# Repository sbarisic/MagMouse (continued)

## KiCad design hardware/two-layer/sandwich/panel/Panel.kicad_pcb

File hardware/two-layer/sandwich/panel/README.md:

# Three-board quotation panel

One 238 × 114 mm, two-layer panel contains one Lower, Upper and Wheel
board. Five panels provide five complete sets. The individual board outlines,
component positions and copper are preserved by translation; nets are isolated
between boards. The panel uses 2 mm routed gaps, 5 mm tabs and 0.6 mm mousebites
on 0.9 mm pitch. The drill row lies outside each finished board outline.

The November circuit correction moves two Wheel tabs to clear the revised
copper: Wheel now has two tabs on its top edge and two on its bottom edge.
The individual board geometry, mounting holes and harness positions are unchanged.

Upload `MagMouse-panel-gerbers.zip` as **Panel by Customer**, **3 designs**,
**5 panels**, FR4, 1.6 mm, 1 oz, green/white, ENIG 1 µin, 0.30 mm minimum via
drill and tented vias. Components, assembly and stencil are separate.

`panelize.py` generates this folder from the three individual boards and checks
exact translated pads, traces, drills and filled copper; connected substrate;
router access; and native KiCad DRC. `panel-manifest.json` records source hashes.
The individual boards also pass ERC, DRC and schematic parity checks, with zero
unconnected nets and zero via-hole/SMD-pad intersections.

This is a quotation package. Supplier CAM approval and prototype electrical,
thermal and enclosure-fit checks remain necessary before production release.

The former Encoder position is panel waste, without its slots or mouse bites.
The three remaining boards retain their positions and outlines.

`Panel-top.png` and `Panel-bottom.png` show copper, fills, pads, vias, silkscreen
and routed edges across the entire panel. The bottom plot is mirrored to show
the physical underside. SVG originals allow inspection at arbitrary zoom.
Regenerate with `../render_panel.py`.

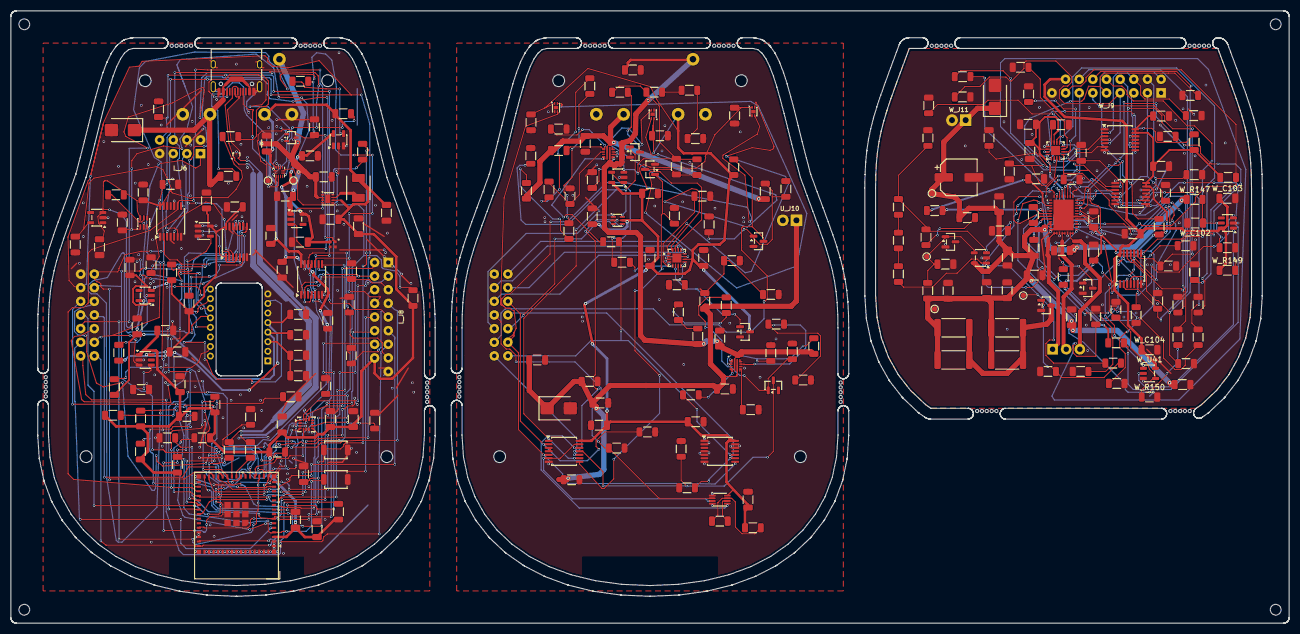
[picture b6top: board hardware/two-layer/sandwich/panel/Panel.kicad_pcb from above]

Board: 2 copper layers, 238.0 x 114.0 mm, 345 parts (0 on the bottom side), 182 nets.

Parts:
L_C1, L_C2, L_C3, L_C5, L_C23, L_C73, L_C74, L_C77, L_C78: 10uF/25V; C_1206_3216Metric
L_C4, L_C55, L_C63, L_C64: 1uF/50V; C_1206_3216Metric
L_C6, L_C22, L_C53, L_C70, L_C75, L_C76, L_C80, L_C83, L_C85, L_C86, L_C87: 100nF; C_1206_3216Metric
L_C71, L_C81, L_C82: 2.2uF/10V; C_1206_3216Metric
L_C72: 10nF; C_1206_3216Metric_OneSideSilk
L_C79: 1nF/50V; C_1206_3216Metric
L_C84: 4.7uF/10V; C_1206_3216Metric
L_C105: 100nF/50V; C_1206_3216Metric
L_D1: SMBJ12A; D_SMB
L_D5: SK6805-EC15; OPSCO_SK6805_EC15
L_H101, L_H102, L_H103, L_H104: M2 clearance / 5mm support envelope; MountingHole_2.2mm_M2_5mm_Envelope
L_J1: TYPE-C-31-M-12; USB_C_Receptacle_HRO_TYPE-C-31-M-12
L_J6: GB1806 AS5048A encoder wires; Wire_Signal_2x04_P2.54mm
L_J8: Wheel 17-wire signals / 2 GND; Wire_Wheel_17_P2.54mm
L_J101: Stack signals / 14 wires; Wire_Stack_Signal_14
L_J103: Stack power / 5 wires; Wire_Stack_Power_5
L_L1: SRP4020CC-3R3M; L_Bourns_SRP4020CC
L_R3, L_R4, L_R7, L_R72, L_R73, L_R74, L_R75, L_R76, L_R77, L_R78, L_R79, L_R80, L_R99, L_R126, L_R127, L_R130, L_R131, L_R135: 10k; R_1206_3216Metric
L_R5, L_R6: 33R; R_1206_3216Metric
L_R25: 887k; R_1206_3216Metric
L_R26, L_R27, L_R101, L_R110, L_R129, L_R133, L_R134, L_R136: 100k; R_1206_3216Metric
L_R28: 1k; R_1206_3216Metric
L_R125: 0R; R_1206_3216Metric
L_R128: 330R; R_1206_3216Metric
L_R132: 39R; R_1206_3216Metric
L_R141, L_R142, L_R143: 33k; R_1206_3216Metric
L_SW1: RESET; SW_SPST_TS-1088-xR020
L_SW2: BOOT; SW_SPST_TS-1088-xR020
L_TP38: RGB_5V; TestPoint_Pad_D1.0mm
L_TP39: RGB_DIN; TestPoint_Pad_D1.0mm
L_U1: TPD2EUSB30DRTR; Texas_DRT-3
L_U2: TPS62162DSGR; Texas_DSG0008A_WSON-8-1EP_2x2mm_P0.5mm_EP0.9x1.6mm
L_U3: ESP32-S3-MINI-1-N8; ESP32-S2-MINI-1
L_U11: TUSB320LAIRWBR; Texas_X2QFN-12_1.6x1.6mm_P0.4mm
L_U20: TPD2E2U06DCKR; SOT-323_SC-70
L_U25, L_U29, L_U37: 74LVC125APW,118; TSSOP-14_4.4x5mm_P0.65mm
L_U28: TPS22919DCKR; SOT-363_SC-70-6
L_U32: ICM-42688-P; LGA-14_3x2.5mm_P0.5mm_LayoutBorder3x4y
L_U33: TPS7A2450DBVR; SOT-23-5
L_U34: SN74LV1T34DBVR; SOT-23-5
L_U35: PMW3360DM-T2QU; PixArt_PMW3360DM_T2QU
L_U36: TLV75519PDBVR; SOT-23-5
L_U38: TPS22918DBVR; SOT-23-6
L_U39: SN74LVC1G125DBVR; SOT-23-5
L_U42: TLV75533PDBVR; SOT-23-5
MB1_1, MB1_2, MB1_3, MB1_4, MB1_5, MB2_1, MB2_2, MB2_3, MB2_4, MB2_5, MB3_1, MB3_2, MB3_3, MB3_4, MB3_5, MB4_1, MB4_2, MB4_3, MB4_4, MB4_5, MB5_1, MB5_2, MB5_3, MB5_4, MB5_5, MB6_1, MB6_2, MB6_3, MB6_4, MB6_5, MB7_1, MB7_2, MB7_3, MB7_4, MB7_5, MB8_1, MB8_2, MB8_3, MB8_4, MB8_5, MB9_1, MB9_2, MB9_3, MB9_4, MB9_5, MB10_1, MB10_2, MB10_3, MB10_4, MB10_5, MB11_1, MB11_2, MB11_3, MB11_4, MB11_5, MB12_1, MB12_2, MB12_3, MB12_4, MB12_5: NPTH
TOOL1, TOOL2, TOOL3, TOOL4: NPTH
U_C16, U_C17, U_C18, U_C28, U_C29, U_C31, U_C32, U_C33, U_C34, U_C35, U_C36: 100nF; C_1206_3216Metric
U_C19, U_C20, U_C21, U_C24, U_C27, U_C89: 1uF/50V; C_1206_3216Metric
U_C25, U_C26: 10nF; C_1206_3216Metric
U_C37, U_C38, U_C39, U_C40, U_C88: 10uF/25V; C_1206_3216Metric
U_D2: SMBJ6.0A; D_SMB
U_D3, U_D4: BAT54-7-F; SOT-23
U_H105, U_H106, U_H107, U_H108: M2 clearance / 5mm support envelope; MountingHole_2.2mm_M2_5mm_Envelope
U_J10: Soldered wires Power_1x02; Wire_Power_1x02_P2.54mm
U_J102: Stack signals / 14 wires; Wire_Stack_Signal_14
U_J104: Stack power / 5 wires; Wire_Stack_Power_5
U_Q1, U_Q2, U_Q3: 2N7002; SOT-23
U_R29, U_R41, U_R65, U_R68: 22.1k; R_1206_3216Metric
U_R30, U_R36, U_R37, U_R38, U_R46, U_R47, U_R48, U_R49, U_R61, U_R70: 10k; R_1206_3216Metric
U_R31, U_R32, U_R33, U_R34, U_R35, U_R40, U_R62, U_R63, U_R66, U_R67, U_R71: 100k; R_1206_3216Metric
U_R39: 11k; R_1206_3216Metric
U_R42, U_R43, U_R56, U_R57, U_R60: 3.3k; R_1206_3216Metric
U_R44, U_R45, U_R64, U_R69: 1k; R_1206_3216Metric
U_R58: 33R; R_1206_3216Metric
U_R59: 4.7k; R_1206_3216Metric
U_U7, U_U8, U_U9: TMAG5253BA2IQDMRR; Texas_X2SON-4-1EP_1.1x1.4mm_P0.5mm_EP0.8x0.6mm
U_U10: ADS7038IRTER; WQFN-16-1EP_3x3mm_P0.5mm_EP1.68x1.68mm
U_U12, U_U13: TPS259470LRPWR; Texas_RPW0010A
U_U14: SN74LVC2G04DCKR; SOT-363_SC-70-6
U_U15: SN74LVC1G123DCUR; VSSOP-8_2.3x2mm_P0.5mm
U_U16, U_U18: SN74LVC08APWR; TSSOP-14_4.4x5mm_P0.65mm
U_U19: TLV9001IDBVR; SOT-23-5
W_C41, W_C42, W_C43, W_C49, W_C51, W_C52, W_C54, W_C65, W_C66: 100nF; C_1206_3216Metric
W_C44, W_C45, W_C68, W_C69: 10uF/25V; C_1206_3216Metric
W_C46, W_C48, W_C56, W_C57, W_C58: 1uF/50V; C_1206_3216Metric
W_C47: 47nF/50V; C_1206_3216Metric
W_C50: 22uF/25V; C_1206_3216Metric
W_C59, W_C60, W_C61, W_C67: 22pF/50V; C_1206_3216Metric
W_C90: 100uF/16V; CP_Elec_6.3x5.9
W_C102: 1nF/50V; C_1206_3216Metric
W_C103, W_C104: 100nF/50V; C_1206_3216Metric
W_D6: SMBJ6.0A; D_SMB
W_J5: GB1806 phase wires; MotorWire_3x1mm_P2.54mm
W_J9: Wheel 17-wire signals / 2 GND; Wire_Wheel_17_P2.54mm
W_J11: Soldered wires Power_1x02; Wire_Power_1x02_P2.54mm
W_Q4: 2N7002; SOT-23
W_Q5: AO3400A; SOT-23
W_R81: 22R; R_1206_3216Metric
W_R82, W_R84, W_R86, W_R98, W_R111, W_R137, W_R138, W_R139, W_R140, W_R148, W_R149: 10k; R_1206_3216Metric
W_R83, W_R89, W_R90, W_R91, W_R92, W_R94, W_R95, W_R96, W_R97, W_R100, W_R112, W_R114, W_R120, W_R150: 100k; R_1206_3216Metric
W_R87, W_R88, W_R146: 4.7k; R_1206_3216Metric
W_R102, W_R103, W_R104: 330R; R_1206_3216Metric
W_R105, W_R106, W_R107, W_R108, W_R109: 0R; R_1206_3216Metric
W_R113: 34.8k; R_1206_3216Metric
W_R115, W_R116, W_R117: 1M; R_1206_3216Metric
W_R119: 100R; R_1206_3216Metric
W_R121, W_R122, W_R123, W_R124: 47R/2W; R_2512_6332Metric
W_R144, W_R145: 33k; R_1206_3216Metric
W_R147: 105k; R_1206_3216Metric
W_TP34: ACT_5V; TestPoint_Pad_D1.0mm
W_TP35: BRAKE_REF; TestPoint_Pad_D1.0mm
W_TP36: BRAKE_OUT; TestPoint_Pad_D1.0mm
W_TP37: GND; TestPoint_Pad_D1.0mm
W_U21: DRV8316RRGFR; Texas_RGF0040E
W_U22: SN74LVC08APWR; TSSOP-14_4.4x5mm_P0.65mm
W_U23: ADS7038IRTER; WQFN-16-1EP_3x3mm_P0.5mm_EP1.68x1.68mm
W_U24: 74LVC125APW,118; TSSOP-14_4.4x5mm_P0.65mm_InsetPin1
W_U26: 74LVC125APW,118; TSSOP-14_4.4x5mm_P0.65mm
W_U30: TLV1811DBVR; SOT-23-5
W_U31: LM4040AIM3-2.5/NOPB; SOT-23
W_U40: TPS3808G01DBVR; SOT-23-6
W_U41: SN74LVC1G08DBVR; SOT-23-5

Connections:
Lower/+3V3: L_C2.1, L_C3.1, L_C5.1, L_C6.1, L_C22.1, L_C23.1, L_C53.1, L_C70.1, L_C71.1, L_C72.1, L_C77.1, L_C78.1, L_J8.16, L_J103.4, L_L1.2, L_R3.1, L_R4.1, L_R7.1, L_R26.1, L_R27.1, L_R72.1, L_R73.1, L_R74.1, L_R75.1, L_R76.1, L_R127.1, L_U2.6, L_U3.3, L_U11.12, L_U25.14, L_U32.5, L_U32.8, L_U38.1
Lower/ACT_DRIVE_EN: L_J8.13, L_J101.13
Lower/ACT_HEARTBEAT: L_J101.7, L_U3.21
Lower/ACT_REQ: L_J101.6, L_U3.20
Lower/ADC2_MISO_LOCAL: L_J8.9, L_R143.1, L_U25.9
Lower/ADC_CS: L_J101.5, L_R7.2, L_U3.14
Lower/BOOT: L_R4.2, L_SW2.1, L_U3.4
Lower/BOOT_SAFE_SPARE: L_R80.1, L_U3.44
Lower/BUCK_SW: L_L1.1, L_U2.7
Lower/CC_OUT1: L_J101.9, L_R26.2, L_U3.18, L_U11.7
Lower/CC_OUT2: L_J101.10, L_R27.2, L_U3.19, L_U11.8
Lower/CC_VBUS_DET: L_R25.2, L_U11.4
Lower/CS_ADC2: L_J8.8, L_R74.2, L_U3.32, L_U25.10
Lower/CS_DRV8316: L_J8.4, L_R76.2, L_U3.34, L_U25.1
Lower/CS_ENCODER: L_R75.2, L_U3.33, L_U25.4, L_U29.9
Lower/CS_IMU: L_R73.2, L_U3.25, L_U32.12
Lower/CS_PAW: L_R72.2, L_U3.6, L_U37.1, L_U37.4, L_U37.10, L_U39.2
Lower/DRV_FAULT_LOCAL_N: L_J8.15, L_R141.1, L_U25.12
Lower/DRV_FAULT_N: L_U3.37, L_U25.11
Lower/DRV_MISO_LOCAL: L_J8.5, L_R142.1, L_U25.2
Lower/ENC_3V3: L_C64.1, L_C105.1, L_R99.1, L_U29.13, L_U29.14, L_U42.5
Lower/ENC_5V: L_C55.1, L_J6.1, L_R125.2, L_U28.6, L_U42.1, L_U42.3
Lower/ENC_CS_LOCAL: L_J6.6, L_R99.2, L_U29.8
Lower/ENC_MISO_LOCAL: L_J6.8, L_R101.1, L_U25.5
Lower/ENC_MOSI_LOCAL: L_J6.5, L_U29.6
Lower/ENC_QOD: L_R125.1, L_U28.5
Lower/ENC_SCLK_LOCAL: L_J6.3, L_U29.3
Lower/GND: L_C1.2, L_C2.2, L_C3.2, L_C4.2, L_C5.2, L_C6.2, L_C22.2, L_C23.2, L_C53.2, L_C55.2, L_C63.2, L_C64.2, L_C70.2, L_C71.2, L_C72.2, L_C73.2, L_C74.2, L_C75.2, L_C76.2, L_C77.2, L_C78.2, L_C79.2, L_C80.2, L_C81.2, L_C82.2, L_C83.2, L_C84.2, L_C85.2, L_C86.2, L_C87.2, L_C105.2, L_D1.2, L_D5.4, L_J1.A1, L_J1.A12, L_J1.B1, L_J1.B12, L_J1.SH, L_J6.2, L_J6.4, L_J6.7, L_J8.1, L_J8.17, L_J101.1, L_J103.1, L_J103.5, L_R77.2, L_R78.2, L_R79.2, L_R80.2, L_R101.2, L_R110.2, L_R126.2, L_R129.2, L_R130.2, L_R134.2, L_R141.2, L_R142.2, L_R143.2, L_SW1.2, L_SW2.2, L_U1.3, L_U2.1, L_U2.4, L_U2.5, L_U2.9, L_U3.1, L_U3.2, L_U3.42, L_U3.43, L_U3.46, L_U3.47, L_U3.48, L_U3.49, L_U3.50, L_U3.51, L_U3.52, L_U3.53, L_U3.54, L_U3.55, L_U3.56, L_U3.57, L_U3.58, L_U3.59, L_U3.60, L_U3.61, L_U3.62, L_U3.63, L_U3.64, L_U3.65, L_U11.3, L_U11.10, L_U11.11, L_U20.3, L_U25.7, L_U25.13, L_U28.2, L_U29.1, L_U29.4, L_U29.7, L_U29.10, L_U29.12, L_U32.6, L_U32.7, L_U33.2, L_U34.3, L_U35.8, L_U36.2, L_U37.7, L_U37.13, L_U38.2, L_U39.1, L_U39.3, L_U42.2
Lower/HALL_EN: L_J101.12, L_R110.1, L_U28.3, L_U33.3, L_U38.3
Lower/IMU_INT1: L_R127.2, L_U3.36, L_U32.4
Lower/IMU_PIN9: L_R126.1, L_U32.9
Lower/LOGIC_PG: L_R28.1, L_U2.8
Lower/MCU_EN: L_C4.1, L_J101.14, L_R3.2, L_R28.2, L_SW1.1, L_U3.45
Lower/MCU_USB_DM: L_R5.1, L_U3.23
Lower/MCU_USB_DP: L_R6.1, L_U3.24
Lower/MOTOR_SPI_MISO: L_U3.31, L_U25.8
Lower/MOTOR_SPI_MOSI: L_J8.7, L_U3.28
Lower/MOTOR_SPI_SCLK: L_J8.6, L_U3.29
Lower/OPT_1V9: L_C82.1, L_C83.1, L_R132.1, L_U35.4, L_U36.5
Lower/OPT_3V3: L_C80.1, L_C81.1, L_C86.1, L_C87.1, L_R131.1, L_R133.1, L_R135.1, L_R136.1, L_U35.5, L_U36.1, L_U36.3, L_U37.14, L_U38.6, L_U39.5
Lower/OPT_CS_N: L_R131.2, L_U35.13, L_U39.4
Lower/OPT_CTRL: L_R79.1, L_U3.26, L_U37.12
Lower/OPT_LED_P: L_R132.2, L_U35.15
Lower/OPT_MISO: L_R135.2, L_U35.12, L_U37.9
Lower/OPT_MOSI: L_R134.1, L_U35.11, L_U37.3
Lower/OPT_RAMP_CT: L_C79.1, L_U38.4
Lower/OPT_RESET_N: L_U35.7, L_U37.11
Lower/OPT_SCLK: L_R133.2, L_U35.10, L_U37.6
Lower/OPT_VDDPIX: L_C84.1, L_C85.1, L_U35.3
Lower/PAW_MOTION_N: L_R136.2, L_U3.35, L_U35.9
Lower/PWR_5V: L_C1.1, L_C73.1, L_J103.3, L_U2.2, L_U2.3, L_U33.1
Lower/RGB_5V: L_C63.1, L_C74.1, L_C75.1, L_C76.1, L_D5.2, L_R130.1, L_TP38.1, L_U28.1, L_U33.5, L_U34.5
Lower/RGB_BUFFER_OUT: L_R128.1, L_U34.4
Lower/RGB_DATA: L_R78.1, L_U3.41, L_U34.2
Lower/RGB_DIN: L_D5.1, L_R128.2, L_R129.1, L_TP39.1
Lower/SENS_REQ: L_J101.8, L_U3.22
Lower/SPI_MISO: L_J101.4, L_U3.17, L_U25.3, L_U25.6, L_U32.1, L_U37.8
Lower/SPI_MOSI: L_J8.3, L_J101.3, L_U3.15, L_U29.5, L_U32.14, L_U37.2
Lower/SPI_SCLK: L_J8.2, L_J101.2, L_U3.16, L_U29.2, L_U32.13, L_U37.5
Lower/USB_CC1: L_J1.A5, L_U11.1, L_U20.1
Lower/USB_CC2: L_J1.B5, L_U11.2, L_U20.2
Lower/USB_DM: L_J1.A7, L_J1.B7, L_R5.2, L_U1.2
Lower/USB_DP: L_J1.A6, L_J1.B6, L_R6.2, L_U1.1
Lower/VBUS_PRESENT_N: L_J101.11, L_U3.5
Lower/VBUS_USB: L_D1.1, L_J1.A4, L_J1.A9, L_J1.B4, L_J1.B9, L_J103.2, L_R25.1
Lower/WHEEL_PWM_A: L_J8.10, L_U3.38
Lower/WHEEL_PWM_B: L_J8.11, L_U3.27
Lower/WHEEL_PWM_C: L_J8.12, L_U3.30
Lower/WHEEL_RUN_REQ: L_J8.14, L_R77.1, L_U3.7
Upper/+3V3: U_C16.1, U_C17.1, U_C18.1, U_C19.1, U_C20.1, U_C28.1, U_C29.1, U_C31.1, U_C32.1, U_C34.1, U_D4.3, U_J104.4, U_R46.1, U_R71.1, U_U7.1, U_U8.1, U_U9.1, U_U10.7, U_U10.10, U_U14.5, U_U15.8, U_U16.14, U_U18.14, U_U19.5
Upper/ACT_5V: U_C37.1, U_C38.1, U_C39.1, U_C40.1, U_D2.1, U_J10.1, U_R67.1, U_R69.1, U_U13.6
Upper/ACT_DRIVE_EN: U_D3.3, U_J102.13, U_R49.1, U_U16.11
Upper/ACT_DVDT: U_C26.1, U_U13.7
Upper/ACT_FAULT_N: U_R45.1, U_U13.4
Upper/ACT_HEARTBEAT: U_J102.7, U_R47.1, U_U15.2
Upper/ACT_ILM: U_R42.1, U_R43.1, U_U13.9
Upper/ACT_OVLO: U_R40.2, U_R41.1, U_U13.2
Upper/ACT_PERMIT: U_U15.5, U_U16.12
Upper/ACT_REQ: U_J102.6, U_R48.1, U_U16.2
Upper/ACT_UVLO: U_D3.1, U_R38.2, U_R39.1, U_U13.1
Upper/ACT_UV_1: U_R36.2, U_R37.1
Upper/ACT_UV_2: U_R37.2, U_R38.1
Upper/ACT_VMON: U_C36.1, U_D4.1, U_R67.2, U_R68.1, U_U10.6
Upper/ADC_CS: U_J102.5, U_U10.11
Upper/ADC_DECAP: U_C21.1, U_U10.8
Upper/ARM_SOURCE: U_U16.3, U_U16.4
Upper/ARM_VALID: U_U15.3, U_U16.6, U_U16.13
Upper/CC_OUT1: U_J102.9, U_U14.1
Upper/CC_OUT2: U_J102.10, U_U14.3
Upper/CC_OUT2_INV: U_U14.4, U_U16.10
Upper/GND: U_C16.2, U_C17.2, U_C18.2, U_C19.2, U_C20.2, U_C21.2, U_C24.2, U_C25.2, U_C26.2, U_C28.2, U_C29.2, U_C31.2, U_C32.2, U_C33.2, U_C34.2, U_C35.2, U_C36.2, U_C37.2, U_C38.2, U_C39.2, U_C40.2, U_C88.2, U_C89.2, U_D2.2, U_J10.2, U_J102.1, U_J104.1, U_J104.5, U_Q1.2, U_Q2.2, U_Q3.2, U_R30.2, U_R35.2, U_R39.2, U_R41.2, U_R42.2, U_R43.2, U_R47.2, U_R48.2, U_R49.2, U_R58.2, U_R62.2, U_R63.2, U_R66.2, U_R68.2, U_R69.2, U_R70.2, U_U7.2, U_U7.5, U_U8.2, U_U8.5, U_U9.2, U_U9.5, U_U10.2, U_U10.3, U_U10.4, U_U10.9, U_U10.17, U_U12.8, U_U13.8, U_U14.2, U_U15.1, U_U15.4, U_U16.7, U_U18.1, U_U18.2, U_U18.4, U_U18.5, U_U18.7, U_U18.12, U_U18.13, U_U19.2
Upper/HALL_EN: U_J102.12, U_U7.3, U_U8.3, U_U9.3, U_U16.5, U_U18.8
Upper/HALL_L: U_U7.4, U_U10.15
Upper/HALL_M: U_U8.4, U_U10.16
Upper/HALL_R: U_U9.4, U_U10.1
Upper/ILM_BASE_1: U_R56.2, U_R57.1
Upper/ILM_BASE_2: U_R57.2, U_R58.1
Upper/ILM_HIGH_D: U_Q2.3, U_R60.2, U_R61.2
Upper/ILM_MED_D: U_Q1.3, U_R59.2
Upper/MCU_EN: U_J102.14, U_R44.2, U_R45.2, U_U18.10
Upper/PWR_5V: U_C88.1, U_C89.1, U_J104.3, U_R36.1, U_R40.1, U_U12.6, U_U13.5
Upper/SENS_REQ: U_J102.8, U_R70.1, U_U18.9
Upper/SOURCE_3A: U_Q2.1, U_R63.1, U_U16.8
Upper/SOURCE_OK: U_Q1.1, U_R62.1, U_U14.6, U_U16.1, U_U16.9
Upper/SPI_MISO: U_J102.4, U_U10.12
Upper/SPI_MOSI: U_J102.3, U_U10.14
Upper/SPI_SCLK: U_J102.2, U_U10.13
Upper/USB_DVDT: U_C25.1, U_U12.7
Upper/USB_FAULT_N: U_R44.1, U_U12.4
Upper/USB_ILM: U_R56.1, U_R59.1, U_R60.1, U_R61.1, U_U12.9, U_U19.3
Upper/USB_IMON_ADC: U_C33.1, U_R64.2, U_U10.5
Upper/USB_IMON_BUF: U_R64.1, U_U19.1, U_U19.4
Upper/USB_OVLO: U_R34.2, U_R35.1, U_U12.2
Upper/USB_OV_1: U_R31.2, U_R32.1
Upper/USB_OV_2: U_R32.2, U_R33.1
Upper/USB_OV_3: U_R33.2, U_R34.1
Upper/USB_UVLO: U_R29.2, U_R30.1, U_U12.1
Upper/VBUS_GATE: U_C35.1, U_Q3.1, U_R65.2, U_R66.1
Upper/VBUS_PRESENT_N: U_J102.11, U_Q3.3, U_R71.2
Upper/VBUS_USB: U_C24.1, U_J104.2, U_R29.1, U_R31.1, U_R65.1, U_U12.5
Upper/WD_CEXT: U_C27.2, U_U15.6
Upper/WD_RCEXT: U_C27.1, U_R46.2, U_U15.7
Wheel/+3V3: W_C51.1, W_C103.1, W_C104.1, W_J9.16, W_R149.1, W_U22.14, W_U40.6, W_U41.5
Wheel/ACT_5V: W_C41.1, W_C42.1, W_C43.1, W_C44.1, W_C45.1, W_C46.2, W_C65.1, W_C68.1, W_C69.1, W_C90.1, W_D6.1, W_J11.1, W_R111.1, W_R112.1, W_R121.1, W_R122.1, W_R123.1, W_R124.1, W_R146.1, W_R147.1, W_TP34.1, W_U21.9, W_U21.10, W_U21.11, W_U30.5
Wheel/ACT_DRIVE_EN: W_J9.13, W_R84.1, W_U21.23, W_U22.1, W_U40.3
Wheel/ADC2_CS_LOCAL: W_R98.2, W_U23.11, W_U26.8
Wheel/ADC2_DECAP: W_C58.1, W_U23.8
Wheel/ADC2_MISO_LOCAL: W_J9.9, W_R100.1, W_U23.12
Wheel/ADC2_MOSI_LOCAL: W_U23.14, W_U26.6
Wheel/ADC2_SCLK_LOCAL: W_U23.13, W_U26.3
Wheel/ADC2_SPARE3: W_R105.1, W_U23.2
Wheel/ADC2_SPARE4: W_R106.1, W_U23.3
Wheel/ADC2_SPARE5: W_R107.1, W_U23.4
Wheel/ADC2_SPARE6: W_R108.1, W_U23.5
Wheel/ADC2_SPARE7: W_R109.1, W_U23.6
Wheel/BRAKE_DIV_TOP: W_R112.2, W_R113.1
Wheel/BRAKE_DRAIN: W_Q5.3, W_R121.2, W_R122.2, W_R123.2, W_R124.2
Wheel/BRAKE_FB_1: W_R115.2, W_R116.1
Wheel/BRAKE_FB_2: W_R116.2, W_R117.1
Wheel/BRAKE_GATE: W_Q5.1, W_R119.2, W_R120.1
Wheel/BRAKE_OUT: W_R115.1, W_R119.1, W_TP36.1, W_U30.1
Wheel/BRAKE_REF: W_C66.1, W_R111.2, W_TP35.1, W_U30.4, W_U31.1
Wheel/BRAKE_SENSE: W_C67.1, W_R113.2, W_R114.1, W_R117.2, W_U30.3
Wheel/CS_ADC2: W_J9.8, W_R145.1, W_U26.9
Wheel/CS_DRV8316: W_J9.4, W_R144.1, W_U24.9
Wheel/DRV_AVDD: W_C48.1, W_C49.1, W_C52.1, W_C54.1, W_C56.1, W_C57.1, W_R82.1, W_R86.1, W_R87.1, W_R88.1, W_R98.1, W_U21.25, W_U21.37, W_U23.7, W_U23.10, W_U24.13, W_U24.14, W_U26.13, W_U26.14
Wheel/DRV_CS_LOCAL: W_R86.2, W_U21.36, W_U24.8
Wheel/DRV_FAULT_LOCAL_N: W_J9.15, W_R88.2, W_R89.1, W_U21.22
Wheel/DRV_INHA: W_R90.1, W_U21.27, W_U22.6
Wheel/DRV_INHB: W_R91.1, W_U21.29, W_U22.8
Wheel/DRV_INHC: W_R92.1, W_U21.31, W_U22.11
Wheel/DRV_MISO_LOCAL: W_J9.5, W_R87.2, W_U21.33
Wheel/DRV_MOSI_LOCAL: W_U21.34, W_U24.6
Wheel/DRV_SCLK_LOCAL: W_U21.35, W_U24.3
Wheel/GND: W_C41.2, W_C42.2, W_C43.2, W_C44.2, W_C45.2, W_C48.2, W_C49.2, W_C50.2, W_C51.2, W_C52.2, W_C54.2, W_C56.2, W_C57.2, W_C58.2, W_C59.2, W_C60.2, W_C61.2, W_C65.2, W_C66.2, W_C67.2, W_C68.2, W_C69.2, W_C90.2, W_C102.2, W_C103.2, W_C104.2, W_D6.2, W_J9.1, W_J9.17, W_J11.2, W_Q4.2, W_Q5.2, W_R83.2, W_R84.2, W_R89.2, W_R90.2, W_R91.2, W_R92.2, W_R94.2, W_R95.2, W_R96.2, W_R97.2, W_R100.2, W_R105.2, W_R106.2, W_R107.2, W_R108.2, W_R109.2, W_R114.2, W_R120.2, W_R137.2, W_R138.2, W_R139.2, W_R140.2, W_R144.2, W_R145.2, W_R146.2, W_R148.2, W_R150.2, W_TP37.1, W_U21.2, W_U21.4, W_U21.12, W_U21.15, W_U21.18, W_U21.26, W_U21.41, W_U22.7, W_U23.9, W_U23.17, W_U24.1, W_U24.4, W_U24.7, W_U24.10, W_U24.12, W_U26.1, W_U26.4, W_U26.7, W_U26.10, W_U26.12, W_U30.2, W_U31.2, W_U40.2, W_U41.3
Wheel/MOTOR_SPI_MOSI: W_J9.7, W_R97.1, W_U26.5
Wheel/MOTOR_SPI_SCLK: W_J9.6, W_R96.1, W_U26.2
Wheel/SPI_MOSI: W_J9.3, W_R95.1, W_U24.5
Wheel/SPI_SCLK: W_J9.2, W_R94.1, W_U24.2
Wheel/WHEEL_BUCK_OUT: W_C50.1, W_R81.2, W_U21.3
Wheel/WHEEL_BUCK_SW: W_R81.1, W_U21.5
Wheel/WHEEL_CP: W_C46.1, W_U21.8
Wheel/WHEEL_CPH: W_C47.1, W_U21.7
Wheel/WHEEL_CPL: W_C47.2, W_U21.6
Wheel/WHEEL_DRVOFF: W_Q4.3, W_R82.2, W_U21.21
Wheel/WHEEL_I_A: W_C59.1, W_R102.2, W_U23.15
Wheel/WHEEL_I_B: W_C60.1, W_R103.2, W_U23.16
Wheel/WHEEL_I_C: W_C61.1, W_R104.2, W_U23.1
Wheel/WHEEL_PHASE_A: W_J5.1, W_U21.13, W_U21.14
Wheel/WHEEL_PHASE_B: W_J5.2, W_U21.16, W_U21.17
Wheel/WHEEL_PHASE_C: W_J5.3, W_U21.19, W_U21.20
Wheel/WHEEL_PWM_A: W_J9.10, W_R138.1, W_U22.4
Wheel/WHEEL_PWM_B: W_J9.11, W_R139.1, W_U22.9
Wheel/WHEEL_PWM_C: W_J9.12, W_R140.1, W_U22.12
Wheel/WHEEL_RUN_EN: W_Q4.1, W_R83.1, W_R150.1, W_U21.28, W_U21.30, W_U21.32, W_U22.5, W_U22.10, W_U22.13, W_U41.4
Wheel/WHEEL_RUN_REQ: W_J9.14, W_R137.1, W_U22.2
Wheel/WHEEL_RUN_REQUESTED: W_U22.3, W_U41.1
Wheel/WHEEL_SOA: W_R102.1, W_U21.40
Wheel/WHEEL_SOB: W_R103.1, W_U21.39
Wheel/WHEEL_SOC: W_R104.1, W_U21.38
Wheel/WHEEL_VM_OK: W_R149.2, W_U40.1, W_U41.2
Wheel/WHEEL_VM_SENSE: W_C102.1, W_R147.2, W_R148.1, W_U40.5
